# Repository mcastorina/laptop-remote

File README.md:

# laptop-remote

## What is it?
This is a simple project that combines a [Trellis button
pad](https://www.adafruit.com/products/1616) and a [nRF8001 BlueTooth
Low Energy](https://www.adafruit.com/products/1697) breakout in order
to run commands remotely on my (linux) laptop. This project uses the
Arduino Uno for the remote, and a shell script as the receiver.

## Motivation
I thought it would be cool to control my laptop when watching a movie
or other media. It also served as a learning experience for the BLE
protocol.

## Dependencies
Arduino Libraries:

* [Adafruit Trellis](https://github.com/adafruit/Adafruit_Trellis_Library)
* [Adafruit BLE UART](https://github.com/adafruit/Adafruit_nRF8001)

Linux commands:

* gatttool

## Status
- [x] Working prototype on breadboard
- [x] Transfer off of Arduino board
- [x] Design PCB
- [ ] Design case
- [ ] Etch PCB
- [ ] Build case
- [ ] Done!

## Future Goals
Because it uses BlueTooth, it doesn't matter /what/ exactly is connecting
to my laptop. That being said, I might write an Android application to
do the same.

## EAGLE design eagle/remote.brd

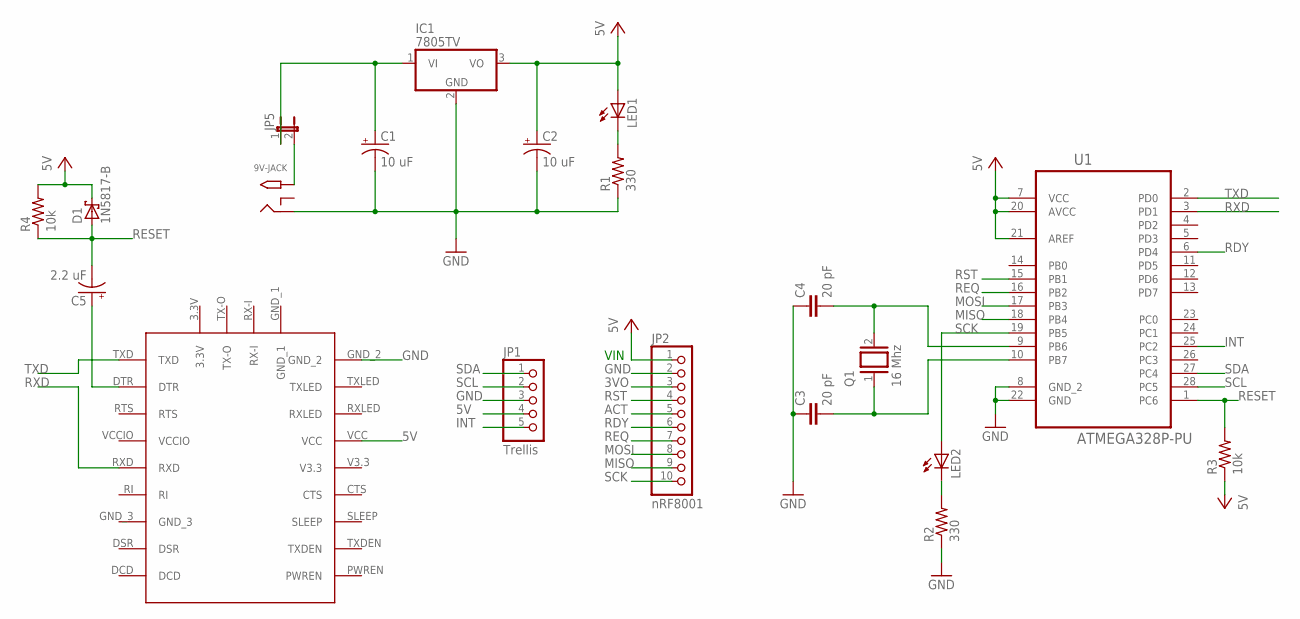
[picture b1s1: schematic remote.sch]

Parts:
9V-JACK: 9V Input; PJ-102A
C1, C2: 10 uF; B45181B
C3, C4: 20 pF; C050-025X075
C5: 2.2 uF; B45181B
D1: 1N5817-B; DO41-7.6
IC1: 7805TV; TO220V
JP1: Trellis; 1X05
JP2: nRF8001; 1X10
JP5: JP1E; JP1
LED1, LED2: LED3MM
Q1: 16 Mhz; QS
R1, R2: 330; RES400MIL
R3, R4: 10k; RES400MIL
U1: ATMEGA328P-PU; DIP254P762X457-28
U$1: FT232

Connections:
3VO: JP2.3
5V: C2.+, D1.C, IC1.3 (VO), JP1.4, JP2.1, LED1.A, R3.1, R4.2, U1.7 (VCC), U1.20 (AVCC), U1.21 (AREF), U$1.VCC
ACT: JP2.5
GND: 9V-JACK.RING, C1.-, C2.-, C3.1, C4.1, IC1.2 (GND), JP1.3, JP2.2, R1.1, R2.1, U1.8 (GND_2), U1.22 (GND), U$1.GND_2
INT: JP1.5, U1.25 (PC2)
MISO: JP2.9, U1.18 (PB4)
MOSI: JP2.8, U1.17 (PB3)
unnamed: C1.+, IC1.1 (VI), JP5.1
unnamed: LED1.K (C), R1.2
unnamed: C3.2, Q1.1, U1.10 (PB7)
unnamed: C4.2, Q1.2, U1.9 (PB6)
unnamed: C5.+, U$1.DTR
unnamed: 9V-JACK.TIP, JP5.2
unnamed: LED2.K (C), R2.2
RDY: JP2.6, U1.6 (PD4)
REQ: JP2.7, U1.16 (PB2)
RESET: C5.-, D1.A, R3.2, R4.1, U1.1 (PC6)
RST: JP2.4, U1.15 (PB1)
RXD: U1.3 (PD1), U$1.RXD
SCK: JP2.10, LED2.A, U1.19 (PB5)
SCL: JP1.2, U1.28 (PC5)
SDA: JP1.1, U1.27 (PC4)
TXD: U1.2 (PD0), U$1.TXD

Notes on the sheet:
VIN

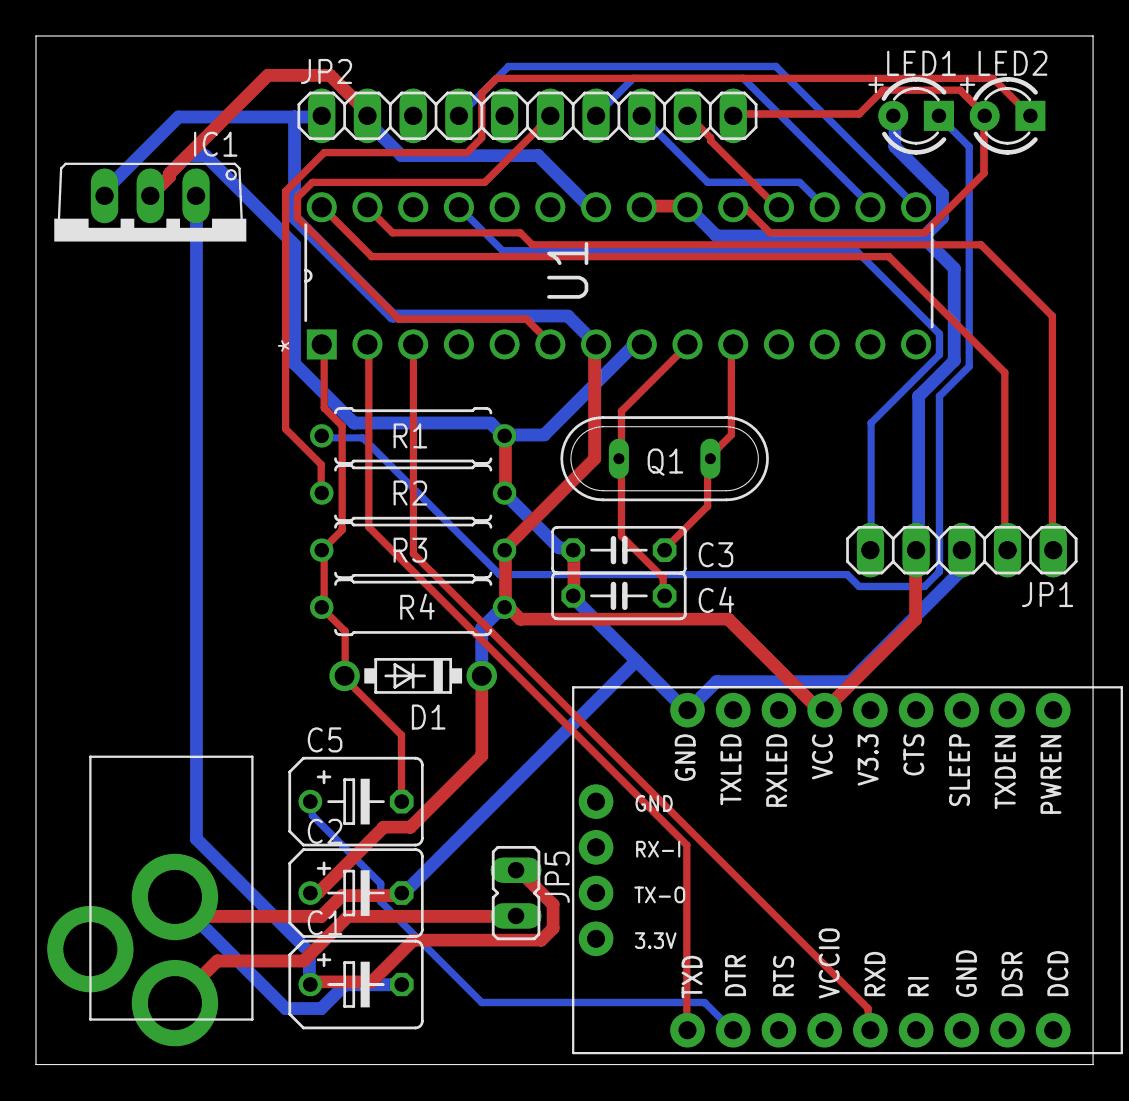
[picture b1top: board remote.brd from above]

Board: 2 copper layers, 58.7 x 57.1 mm, 20 parts (0 on the bottom side), 21 nets.

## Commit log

2016-05-19 Initial commit.
    The current arduino sketch interfaces with the Trellis 4x4 touchpad and
    the nRF8001 BlueTooth Low Energy breakout and sends the key press to the
    laptop (running receiver.sh). The receive script does nothing with the
    values it receives.
2016-05-19 Setup framework for parsing receiver input.
2016-05-19 WIP on arduino code and receiver script.
    Arduino code will now constantly send values if the button is still
    pressed, and the receiver will execute 'xdotool' commands to the move
    the mouse or press keys.
2016-05-20 Receiver is now mapped, and arduino sketch resends button well.
    The receiver script is now mapped to a useful set of commands, and the
    arduino sketch will resend button presses after ~600 ms.
    Overall, it works well, however there is a large flaw: The arduino is
    the one that is advertising and the receiver must connect to it. In
    other words, the remote cannot reconnect to the receiver after turning
    off and back on again.
2016-05-20 Added heartbeat to receiver script.
    The receiver script will restart if the connection is lost or gatttool
    times out waiting for a connection. It is safer to have my laptop do a
    heartbeat than advertise looking for a controller. This way, I know only
    a BLE with the same MAC is connecting to my laptop (and not some random
    BLE).
2016-06-06 Changed some of the command bindings.
2016-06-06 Added Makefile and README.md
2016-06-06 Added license
2016-06-08 Updated Makefile to use /dev/ttyUSB0
2016-07-09 Added eagle schematic and pcb files
2016-08-06 Reworked PCB so it is smaller.
    Because I plan to order the PCB using www.oshpark.com, I used two layers
    and tightened everything up.
2017-07-11 Updated README.md to properly display
